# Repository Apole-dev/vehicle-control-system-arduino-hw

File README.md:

<div align="center">

# Vehicle Control System Hardware Design

</div>

This repository contains the hardware design (schematic and PCB) files and test firmware for the project. The system is based on the **ATmega328P** microcontroller, designed to read, process, and transmit vehicle data over long distances.

## Hardware Features & Integrations

The design is a custom printed circuit board (PCB) operating at a 5V logic level, consolidating various communication modules onto a single board.

* **Power Management:** The system's 5V requirement is supplied by an **LM2596** step-down (buck) regulator module powered via a standard DC Jack.
* **Microcontroller:** DIP-28 package **ATmega328P** utilizing an external crystal oscillator circuit.
* **In-Vehicle Communication (CAN Bus):** Access to the vehicle's network via an **MCP2515** CAN controller module connected through the SPI interface (J3 socket).
* **Telemetry (LoRa):** **LoRa** module integration with a dedicated UART socket (M0, M1, RX, TX, AUX) for long-range wireless data transmission.
* **Location Tracking (GPS):** A GPS module connected to a secondary hardware/software UART line (J5 socket) for speed, location, and timing (PPS) data.
* **Status Indicators:** 6 dedicated debug LEDs connected to pins PC0-PC5 to easily visualize system status, communication packets, or error codes.

## Pinout Summary
* `PC0 - PC5` : Status LEDs (D1 - D6)
* `PB3, PB4, PB5` : SPI Line (MCP2515 CAN Module)
* `PD0, PD1, PD2, PD3, PD4` : LoRa UART and Control (RX, TX, M0, M1, AUX)
* `PD6, PD7` : GPS UART and PPS signals

---

## Schematic

---

## PCB

---
## Contributors

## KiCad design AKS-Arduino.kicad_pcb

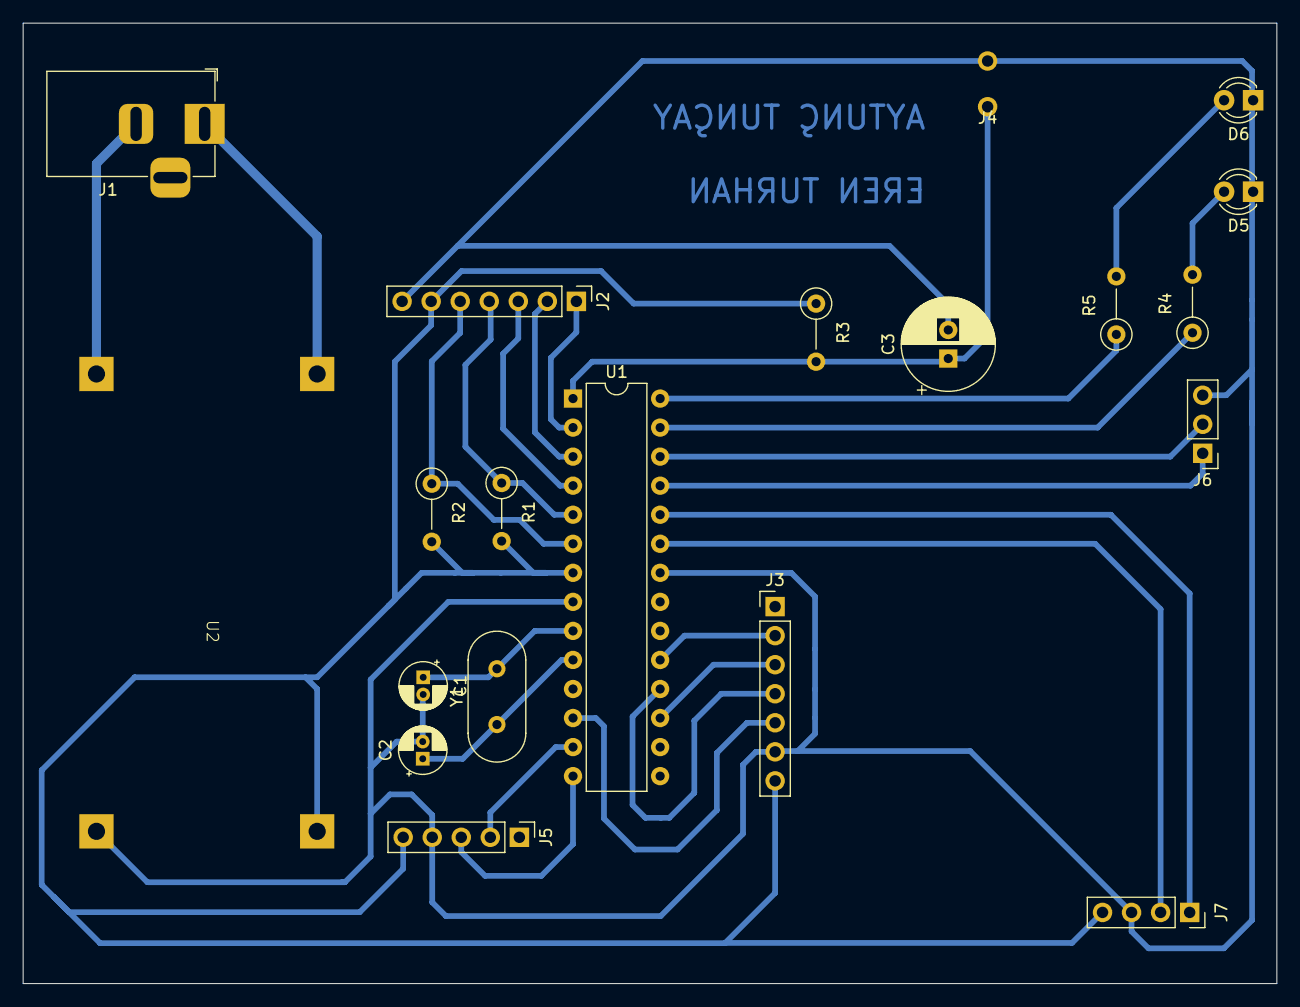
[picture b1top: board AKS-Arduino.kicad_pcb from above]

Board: 2 copper layers, 109.6 x 84.0 mm, 20 parts (0 on the bottom side), 26 nets.

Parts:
C1, C2: 22pF; CP_Radial_D4.0mm_P1.50mm
C3: C_Polarized_US; CP_Radial_D8.0mm_P2.50mm
D5, D6: LED; LED_D3.0mm
J1: Jack-DC; BarrelJack_Horizontal
J2, J3: Conn_01x07_Socket; PinHeader_1x07_P2.54mm_Vertical
J4: Conn_01x02_Socket; PinSocket_1x02_P2.54mm_Vertical
J5: Conn_01x05_Socket; PinHeader_1x05_P2.54mm_Vertical
J6: Conn_01x03_Socket; PinHeader_1x03_P2.54mm_Vertical
J7: Conn_01x04_Socket; PinSocket_1x04_P2.54mm_Vertical
R1, R2, R3, R4, R5: R; R_Axial_DIN0207_L6.3mm_D2.5mm_P5.08mm_Vertical
U1: ATmega328-P; DIP-28_W7.62mm
U2: regulator
Y1: Crystal; Crystal_HC49-4H_Vertical

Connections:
+5V: J2.6, J3.7, J5.5, J7.4, R1.2, R2.2, R3.1, U1.7 (VCC), U2.3 (OUT+)
AUX: J2.5, R2.1, U1.6 (PD4)
CS: J3.5, U1.12 (PD6)
GND: C1.2, C2.2, C3.2, D5.1 (K), D6.1 (K), J2.7, J3.6, J4.2, J5.4, J6.3, J7.3, U1.8 (GND), U1.22 (GND), U2.4 (OUT-)
M0: J2.1, U1.2 (PD0)
M1: J2.2, U1.3 (PD1)
unnamed: D5.2 (A), R4.2
unnamed: D6.2 (A), R5.2
unnamed: R4.1, U1.27 (PC4)
unnamed: R5.1, U1.28 (PC5)
unnamed: J1.1, U2.1 (IN+)
unnamed: J1.2, U2.2 (IN-)
Nextion RX: J7.1, U1.24 (PC1)
Nextion TX: J7.2, U1.23 (PC0)
OSC1: C1.1, U1.9 (XTAL1/PB6), Y1.2
OSC2: C2.1, U1.10 (XTAL2/PB7), Y1.1
RESET: C3.1, J4.1, R3.2, U1.1 (~RESET/PC6)
RXD: J2.3, U1.4 (PD2)
RXDGPS: J5.2, U1.13 (PD7)
SCK: J3.2, U1.19 (PB5)
SI: J3.3, U1.17 (PB3)
SO: J3.4, U1.18 (PB4)
Serial RX: J6.1, U1.25 (PC2)
Serial TX: J6.2, U1.26 (PC3)
TXD: J2.4, R1.1, U1.5 (PD3)
TXDGPS: J5.3, U1.14 (PB0)

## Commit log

2025-03-27 Modules added
2025-03-28 Images added
2025-04-28 Version 1 Last Update
2026-04-05 Revise README with project details and contributors
    Updated project title, added hardware features, pinout summary, and contributor section.
